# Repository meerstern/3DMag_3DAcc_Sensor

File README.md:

# 3D加速度/3D磁力センサ変換基板　
# 3D Magnetometer & 3D Accelerometer Board

## 概要 
  * ST製3D加速度/3D磁力センサ[ISM303DAC][1]を搭載した変換基板です 
  * 1つのセンサで3方向の磁界チャンネルと3方向の加速チャンネルを検出可能です    
  * 変換基板に電圧レベル変換を搭載しているため、3.3V/5V系に直結可能です
  * I2C/SPI/INTすべてのピンで電圧レベル変換を介してアクセス可能です  
  * I2CはGrove互換コネクタを搭載しています  
  * Arduino Uno等で利用可能なサンプルコードがあります  

## 仕様  
  * 磁界センサは最大±50ガウス磁気感度があります   
  * 加速度センサは±2/±4/±8/±16gから選択可能です  
  * 16bit分解能、256個のFIFOメモリを搭載しています    
  * SPI/I2Cシリアルインターフェイスを利用可能です
  * 急降下、動作、磁場検出のためのプログラマブルな割り込みに対応    
  * 電源電圧DC2.5V-5.0V  
  * サイズ30mm x25mm (突起部、コネクタ除く)

## 外観

[1]: https://www.st.com/ja/mems-and-sensors/ism303dac.html

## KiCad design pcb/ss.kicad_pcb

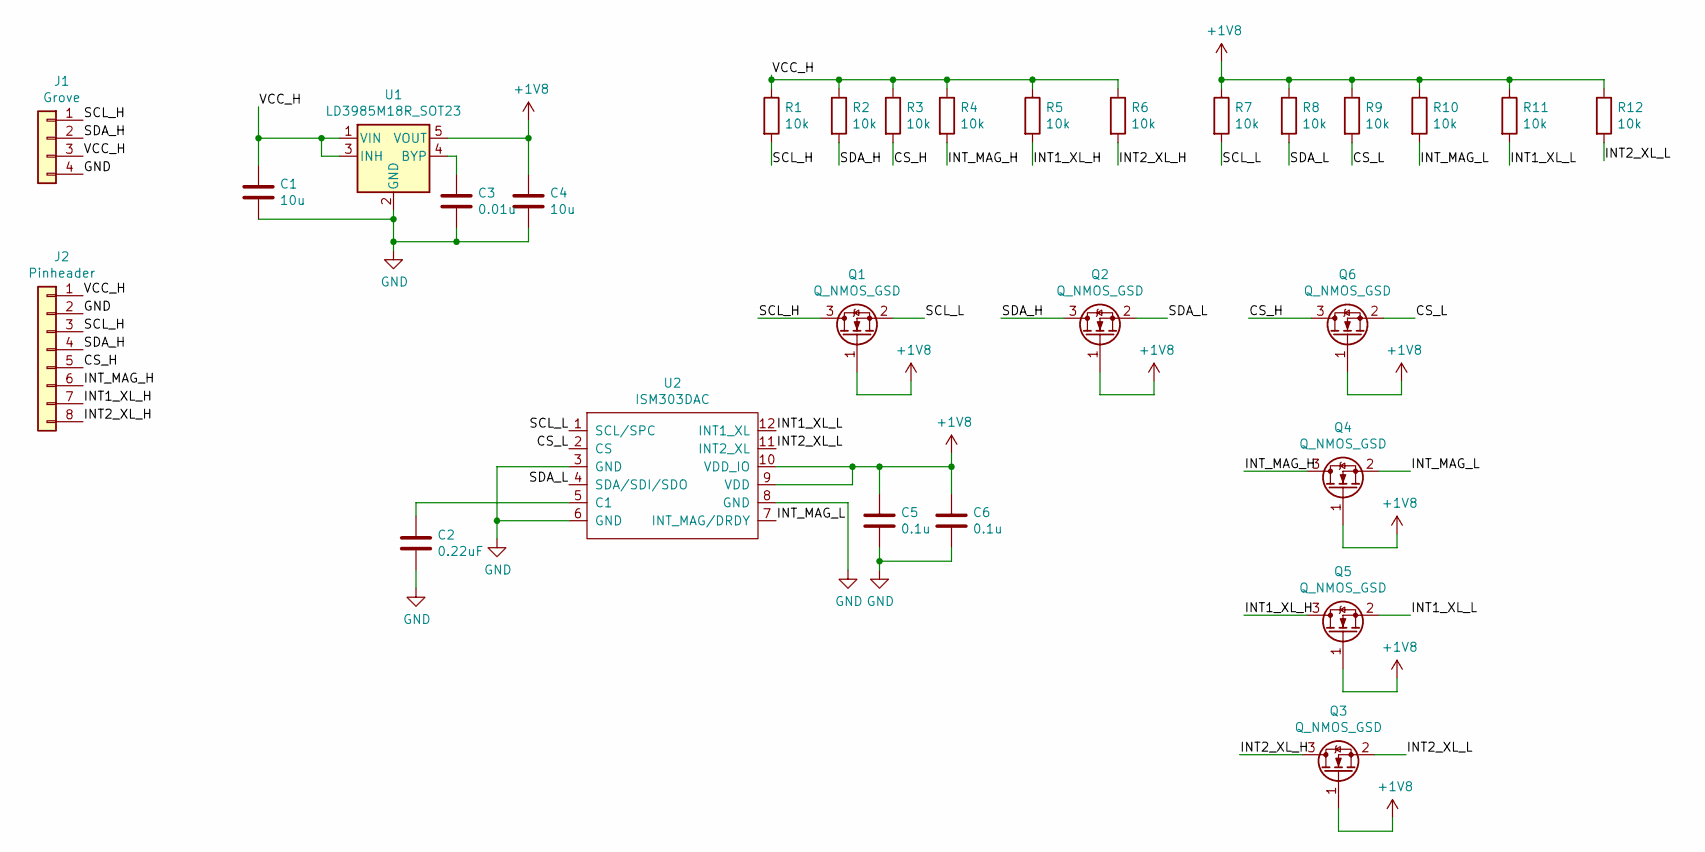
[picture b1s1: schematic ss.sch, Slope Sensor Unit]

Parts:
C1, C4: 10u; C_0805_2012Metric
C2: 0.22uF; C_0603_1608Metric
C3: 0.01u; C_0603_1608Metric
C5, C6: 0.1u; C_0603_1608Metric
J1: Grove; GROVE
J2: Pinheader; PinHeader_1x08_P2.54mm_Vertical
Q1, Q2, Q3, Q4, Q5, Q6: Q_NMOS_GSD; SOT-23
R1, R2, R3, R4, R5, R6, R7, R8, R9, R10, R11, R12: 10k; R_0603_1608Metric
U1: LD3985M18R_SOT23; SOT-23-5
U2: ISM303DAC; LGA12

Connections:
+1V8: C4.1, C5.1, C6.1, Q1.1 (G), Q2.1 (G), Q3.1 (G), Q4.1 (G), Q5.1 (G), Q6.1 (G), R7.1, R8.1, R9.1, R10.1, R11.1, R12.1, U1.5 (VOUT), U2.9 (VDD), U2.10 (VDD_IO)
/CS_H: J2.5, Q6.3 (D), R3.2
/CS_L: Q6.2 (S), R9.2, U2.2 (CS)
/INT1_XL_H: J2.7, Q5.3 (D), R5.2
/INT1_XL_L: Q5.2 (S), R11.2, U2.12 (INT1_XL)
/INT2_XL_H: J2.8, Q3.3 (D), R6.2
/INT2_XL_L: Q3.2 (S), R12.2, U2.11 (INT2_XL)
/INT_MAG_H: J2.6, Q4.3 (D), R4.2
/INT_MAG_L: Q4.2 (S), R10.2, U2.7 (INT_MAG/DRDY)
/SCL_H: J1.1, J2.3, Q1.3 (D), R1.2
/SCL_L: Q1.2 (S), R7.2, U2.1 (SCL/SPC)
/SDA_H: J1.2, J2.4, Q2.3 (D), R2.2
/SDA_L: Q2.2 (S), R8.2, U2.4 (SDA/SDI/SDO)
/VCC_H: C1.1, J1.3, J2.1, R1.1, R2.1, R3.1, R4.1, R5.1, R6.1, U1.1 (VIN), U1.3 (INH)
GND: C1.2, C2.2, C3.2, C4.2, C5.2, C6.2, J1.4, J2.2, U1.2 (GND), U2.3 (GND), U2.6 (GND), U2.8 (GND)
unnamed: C2.1, U2.5 (C1)
unnamed: C3.1, U1.4 (BYP)

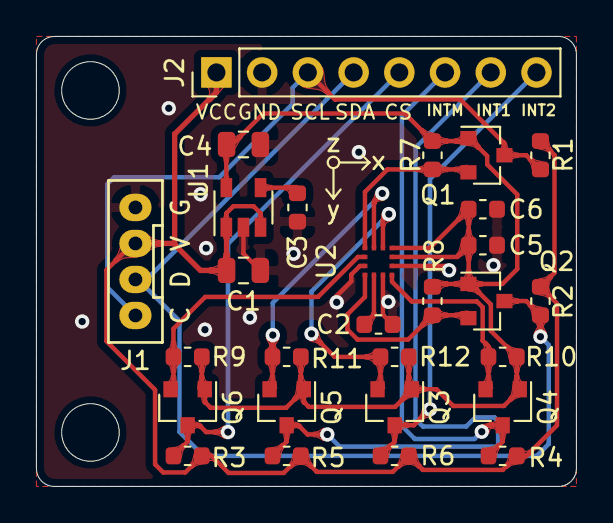
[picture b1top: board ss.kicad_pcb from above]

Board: 2 copper layers, 30.0 x 25.0 mm, 30 parts (0 on the bottom side), 17 nets.

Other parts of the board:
REF1, REF2: MountingHole_3.2mm_M3

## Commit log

2025-02-20 Add Sample Code
2025-03-10 Add images
2025-03-10 Add pcb
2025-03-10 Add Circuit
2025-03-23 Update Figures
